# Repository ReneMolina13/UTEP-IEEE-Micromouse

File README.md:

<div id="top"></div>

<!-- PROJECT LOGO -->
</br>
<div align="center">
  
  <h3 align="center">UTEP IEEE Micromouse</h3>
   <p align="center">
     UTEP IEEE Micromouse project repository
     </br>
     <a href="workshops/Intro to micromouse presentation.pdf"><strong>See intro presentation</strong></a>
     </br>
  </p>
</div>

<!-- TABLE OF CONTENTS -->
<details>
  <summary>Table of Contents</summary>
  <ol>
    <li><a href="#about-the-project">About The Project</a></li>
    <li><a href="#contributing">Contributing</a></li>
    <li><a href="#license">License</a></li>
    <li><a href="#contact">Contact</a></li>
    <li><a href="#acknowledgments">Acknowledgments</a></li>
  </ol>
</details>

<!-- ABOUT THE PROJECT -->
## About The Project
</br>
<div align="left">
  IEEE UTEP Micromouse repository where you can find template code, schematics and workshops
  to build and get your mouse working. This repository was designed to be used with the micromouse
  kit shown in the schematics folder. The workshops will guide you through the necessary code to 
  have your mouse solving a micromouse maze.
  
  Take a look at:
  
  - [Schematics](micromouse_arduino_nano_kit/Micromouse_Arduino_Nano.pdf)
  - [Workshops](workshops/)
  - [Code](code_template/)
</div>

<p align="right">(<a href="#top">back to top</a>)</p>

<!-- CONTRIBUTING -->
## Contributing

To contribute, please fork the project and send a pull request or talk to any of the UTEP IEEE officers. For any other questions please use the contact info at the bottom to contact the owner of this repository.
<p align="right">(<a href="#top">back to top</a>)</p>

<!-- LICENSE -->
## License

Distributed under the MIT License. See `LICENSE.txt` for more information.

<p align="right">(<a href="#top">back to top</a>)</p>

<!-- CONTACT -->
## Contact

Alejandro Martinez Acosta - amartinezacosta@miners.utep.edu

Project Link: [https://github.com/amartinezacosta/UTEP-IEEE-Micromouse](https://github.com/amartinezacosta/UTEP-IEEE-Micromouse)

<p align="right">(<a href="#top">back to top</a>)</p>

<!-- ACKNOWLEDGMENTS -->
## Acknowledgments
[University of Texas at El Paso](https://www.utep.edu/)

[IEEE University of Texas at El Paso branch](https://edu.ieee.org/us-utep/)

<p align="right">(<a href="#top">back to top</a>)</p>

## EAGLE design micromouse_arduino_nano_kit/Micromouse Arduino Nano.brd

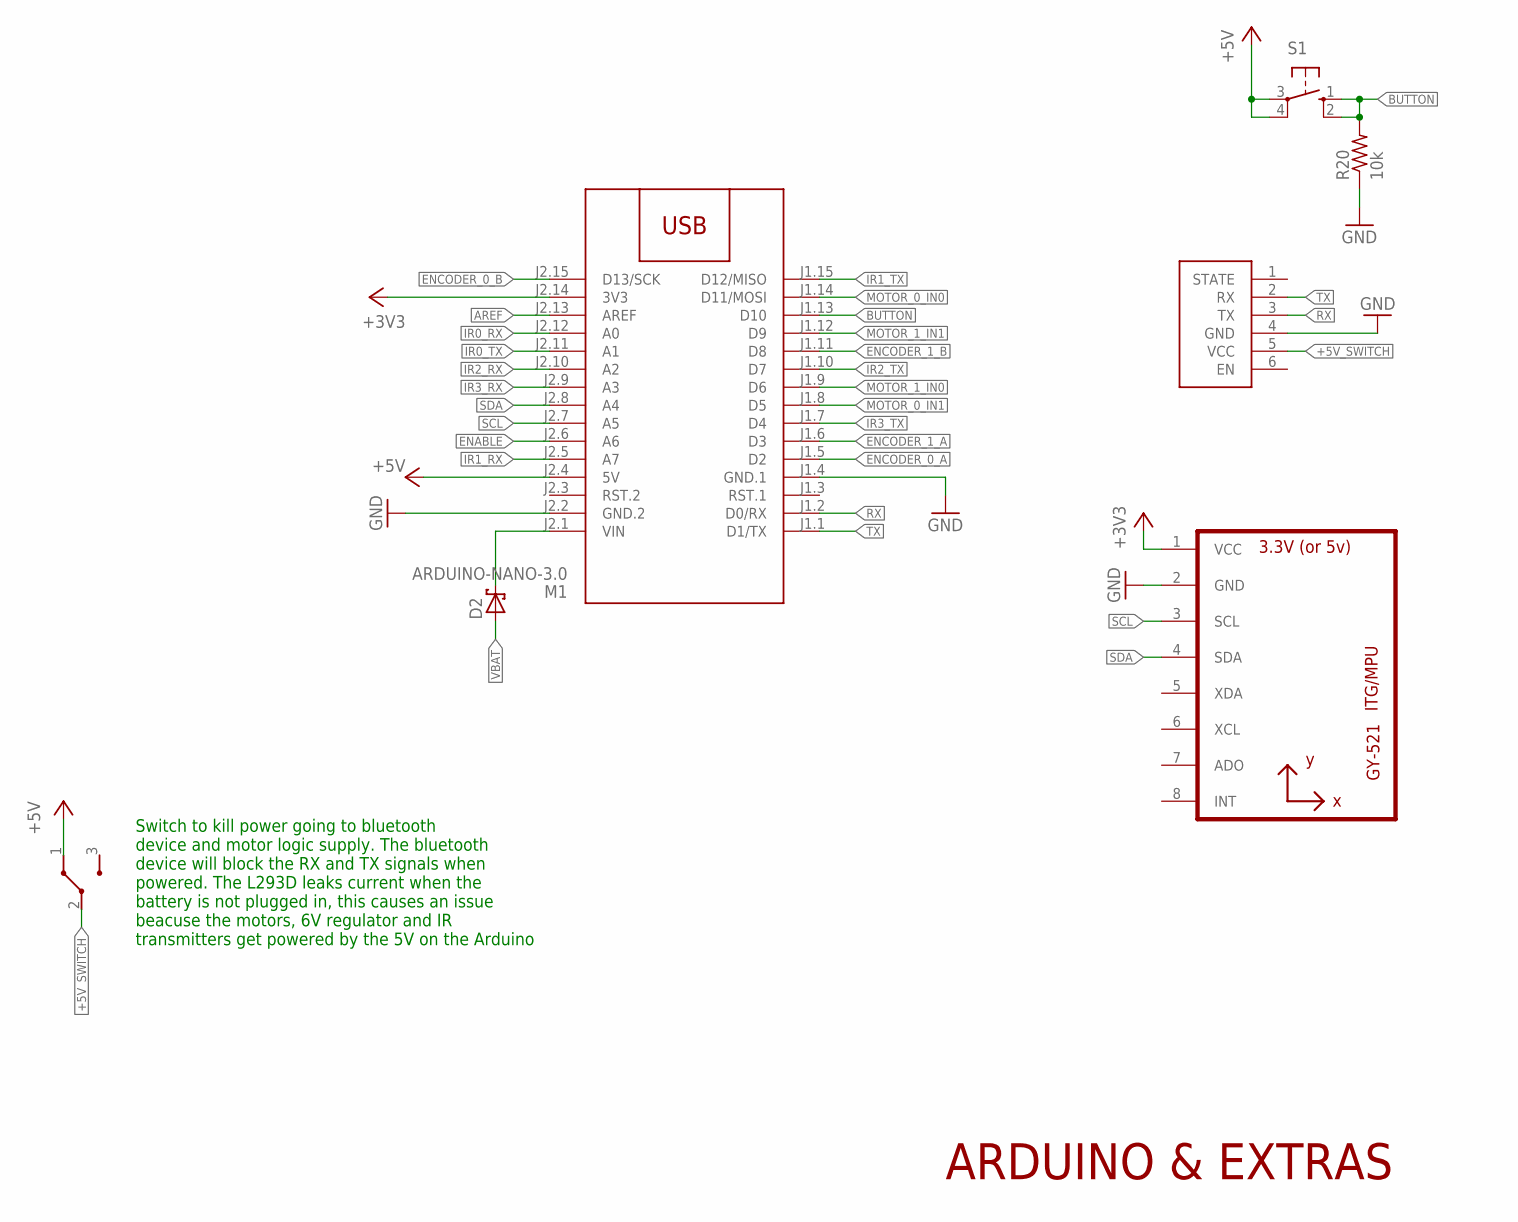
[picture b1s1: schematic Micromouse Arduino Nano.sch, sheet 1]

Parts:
D2: SCHOTTKY-DIODEDO41-7; DO41-7
M1: ARDUINO-NANO-3.0
R20: 10k; 0207/2V
S1: 10-XX; B3F-10XX
U1: GY-521MPU6050; GY-521
U$9: HC-05
U$10: K3-1260D

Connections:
+3V3: M1.J2.14 (3V3), U1.1 (VCC)
+5V: M1.J2.4 (5V), S1.3, S1.4 (P1), U$10.1; also elsewhere on the board
+5V_SWITCH: U$9.5 (VCC), U$10.2; also elsewhere on the board
AREF: M1.J2.13 (AREF)
BUTTON: M1.J1.13 (D10), R20.2, S1.1 (S), S1.2 (S1)
ENABLE: M1.J2.6 (A6); also elsewhere on the board
ENCODER_0_A: M1.J1.5 (D2); also elsewhere on the board
ENCODER_0_B: M1.J2.15 (D13/SCK); also elsewhere on the board
ENCODER_1_A: M1.J1.6 (D3); also elsewhere on the board
ENCODER_1_B: M1.J1.11 (D8); also elsewhere on the board
GND: M1.J1.4 (GND.1), M1.J2.2 (GND.2), R20.1, U1.2 (GND), U$9.4 (GND); also elsewhere on the board
IR0_RX: M1.J2.12 (A0); also elsewhere on the board
IR0_TX: M1.J2.11 (A1); also elsewhere on the board
IR1_RX: M1.J2.5 (A7); also elsewhere on the board
IR1_TX: M1.J1.15 (D12/MISO); also elsewhere on the board
IR2_RX: M1.J2.10 (A2); also elsewhere on the board
IR2_TX: M1.J1.10 (D7); also elsewhere on the board
IR3_RX: M1.J2.9 (A3); also elsewhere on the board
IR3_TX: M1.J1.7 (D4); also elsewhere on the board
MOTOR_0_IN0: M1.J1.14 (D11/MOSI); also elsewhere on the board
MOTOR_0_IN1: M1.J1.8 (D5); also elsewhere on the board
MOTOR_1_IN0: M1.J1.9 (D6); also elsewhere on the board
MOTOR_1_IN1: M1.J1.12 (D9); also elsewhere on the board
unnamed: D2.C, M1.J2.1 (VIN)
RX: M1.J1.2 (D0/RX), U$9.3 (TX)
SCL: M1.J2.7 (A5), U1.3 (SCL)
SDA: M1.J2.8 (A4), U1.4 (SDA)
TX: M1.J1.1 (D1/TX), U$9.2 (RX)
VBAT: D2.A; also elsewhere on the board

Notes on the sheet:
Switch to kill power going to bluetooth device and motor logic supply. The bluetooth device will block the RX and TX signals when powered. The L293D leaks current when the battery is not plugged in, this causes an issue beacuse the motors, 6V regulator and IR transmitters get powered by the 5V on t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
ARDUINO & EXTRAS

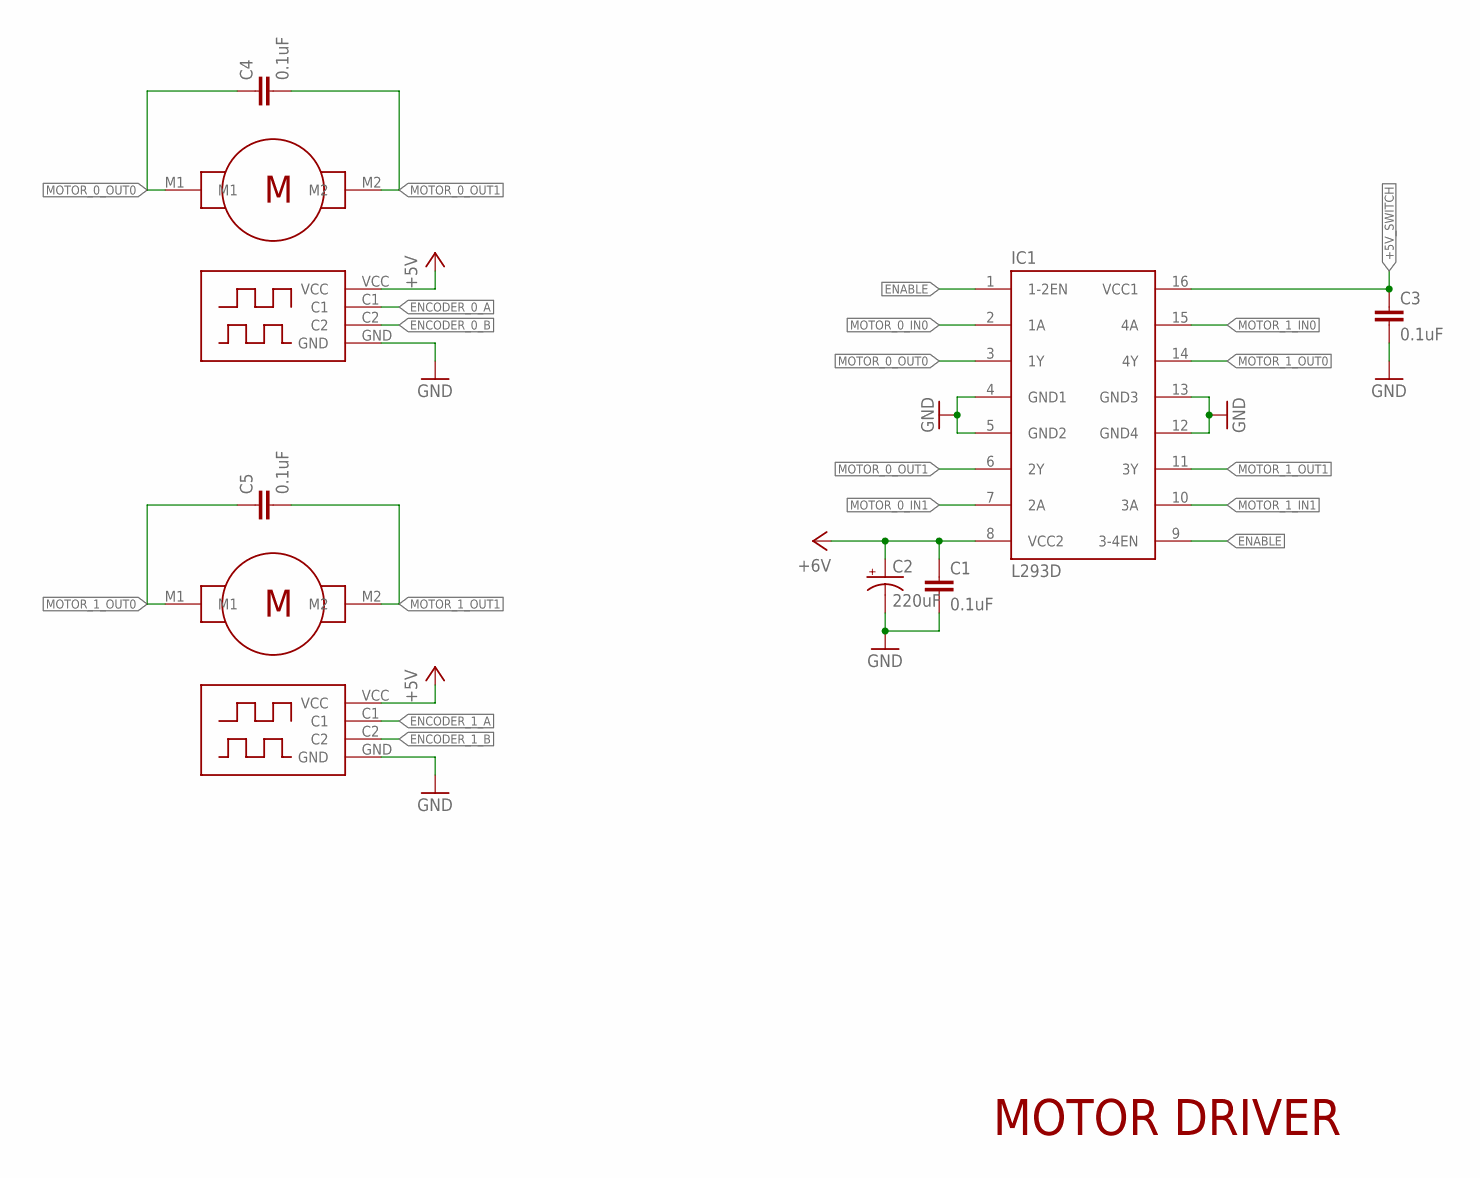
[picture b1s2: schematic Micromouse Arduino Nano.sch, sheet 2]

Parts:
C1, C3, C4, C5: 0.1uF; C050-025X075
C2: 220uF; E2,5-6
IC1: L293D; DIL16
U$1, U$2: DC_MOTOR

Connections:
+5V: U$1.VCC, U$2.VCC; also elsewhere on the board
+5V_SWITCH: C3.1, IC1.16 (VCC1); also elsewhere on the board
ENABLE: IC1.1 (1-2EN), IC1.9 (3-4EN); also elsewhere on the board
ENCODER_0_A: U$1.C1; also elsewhere on the board
ENCODER_0_B: U$1.C2; also elsewhere on the board
ENCODER_1_A: U$2.C1; also elsewhere on the board
ENCODER_1_B: U$2.C2; also elsewhere on the board
GND: C1.2, C2.-, C3.2, IC1.4 (GND1), IC1.5 (GND2), IC1.12 (GND4), IC1.13 (GND3), U$1.GND, U$2.GND; also elsewhere on the board
MOTOR_0_IN0: IC1.2 (1A); also elsewhere on the board
MOTOR_0_IN1: IC1.7 (2A); also elsewhere on the board
MOTOR_0_OUT0: C4.1, IC1.3 (1Y), U$1.M1
MOTOR_0_OUT1: C4.2, IC1.6 (2Y), U$1.M2
MOTOR_1_IN0: IC1.15 (4A); also elsewhere on the board
MOTOR_1_IN1: IC1.10 (3A); also elsewhere on the board
MOTOR_1_OUT0: C5.1, IC1.14 (4Y), U$2.M1
MOTOR_1_OUT1: C5.2, IC1.11 (3Y), U$2.M2
VCC: C1.1, C2.+, IC1.8 (VCC2); also elsewhere on the board

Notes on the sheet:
MOTOR DRIVER

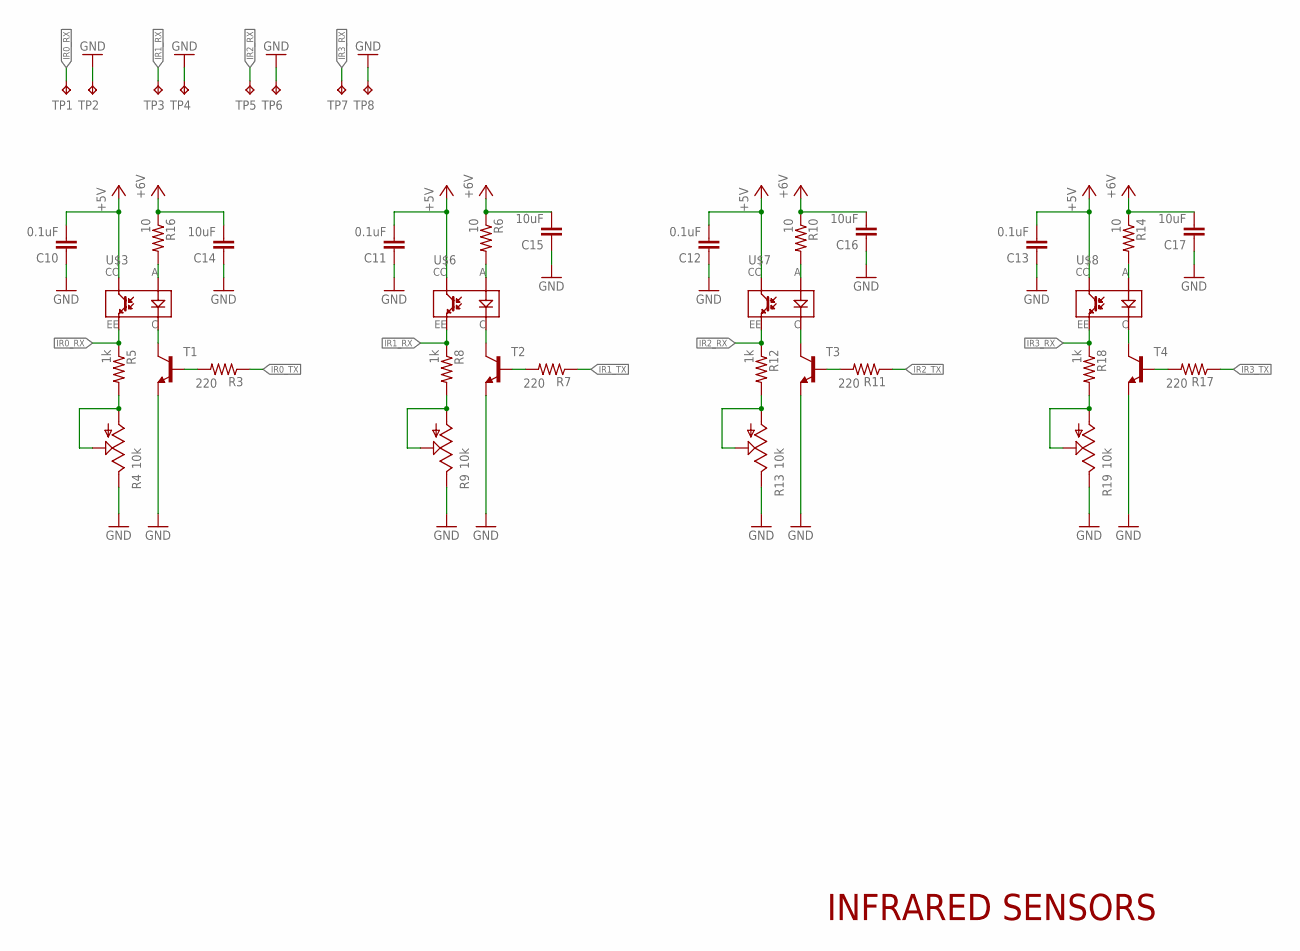
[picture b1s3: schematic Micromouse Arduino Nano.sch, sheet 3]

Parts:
C10, C11, C12, C13: 0.1uF; C050-025X075
C14, C15, C16, C17: 10uF; C050-025X075
R3, R7, R11, R17: 220; 0207/2V
R4, R9, R13, R19: 10k; CT6
R5, R8, R12, R18: 1k; 0207/2V
R6, R10, R14, R16: 10; 0207/2V
T1, T2, T3, T4: 2N4124-NPN-TO92-CBE; TO92-CBE
TP1, TP2, TP3, TP4, TP5, TP6, TP7, TP8: TPPAD1-13; P1-13
U$3, U$6, U$7, U$8: IR_DISTANCE_1X2

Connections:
+5V: C10.2, C11.2, C12.2, C13.2, U$3.CC, U$6.CC, U$7.CC, U$8.CC; also elsewhere on the board
GND: C10.1, C11.1, C12.1, C13.1, C14.1, C15.1, C16.1, C17.1, R4.E, R9.E, R13.E, R19.E, T1.E, T2.E, T3.E, T4.E, TP2.TP, TP4.TP, TP6.TP, TP8.TP; also elsewhere on the board
IR0_RX: R5.1, TP1.TP, U$3.EE; also elsewhere on the board
IR0_TX: R3.1; also elsewhere on the board
IR1_RX: R8.1, TP3.TP, U$6.EE; also elsewhere on the board
IR1_TX: R7.1; also elsewhere on the board
IR2_RX: R12.1, TP5.TP, U$7.EE; also elsewhere on the board
IR2_TX: R11.1; also elsewhere on the board
IR3_RX: R18.1, TP7.TP, U$8.EE; also elsewhere on the board
IR3_TX: R17.1; also elsewhere on the board
unnamed: T1.C, U$3.C
unnamed: R3.2, T1.B
unnamed: R16.2, U$3.A
unnamed: R6.2, U$6.A
unnamed: R4.A, R4.S, R5.2
unnamed: T2.C, U$6.C
unnamed: R7.2, T2.B
unnamed: R8.2, R9.A, R9.S
unnamed: R10.2, U$7.A
unnamed: T3.C, U$7.C
unnamed: R11.2, T3.B
unnamed: R12.2, R13.A, R13.S
unnamed: R14.2, U$8.A
unnamed: T4.C, U$8.C
unnamed: R17.2, T4.B
unnamed: R18.2, R19.A, R19.S
VCC: C14.2, C15.2, C16.2, C17.2, R6.1, R10.1, R14.1, R16.1; also elsewhere on the board

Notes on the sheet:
INFRARED SENSORS

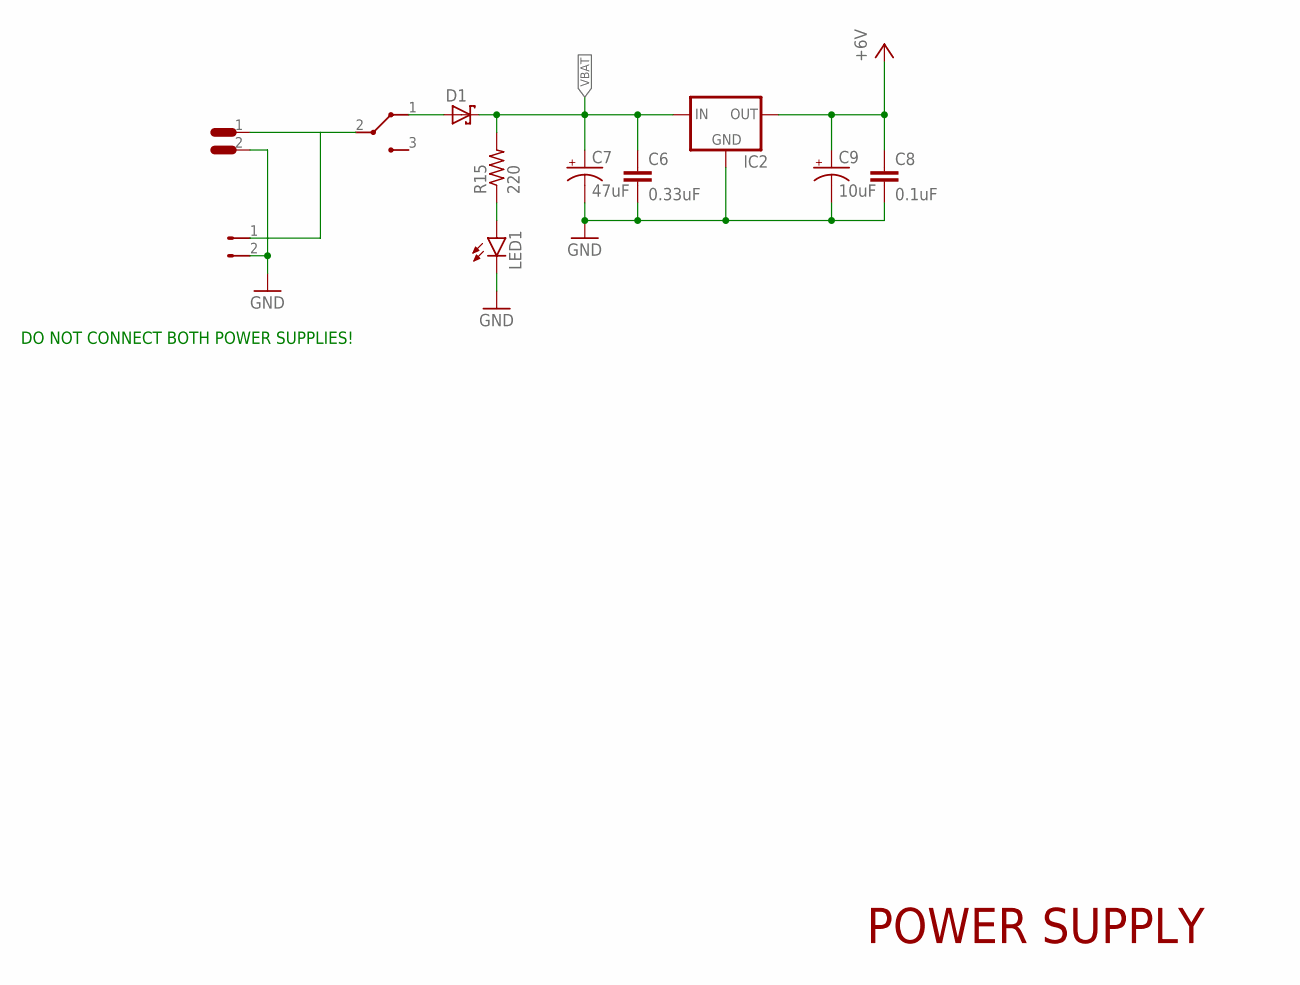
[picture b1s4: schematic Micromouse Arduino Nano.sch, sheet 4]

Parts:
C6: 0.33uF; C050-025X075
C7: 47uF; E2-4
C8: 0.1uF; C050-025X075
C9: 10uF; E2,5-5
D1: SCHOTTKY-DIODEDO41-7; DO41-7
IC2: 78XXS
LED1: LED5MM
R15: 220; 0207/2V
U$4: K3-1260D
U$5: XT30-M
U$12: JST_POWER

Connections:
GND: C6.2, C7.-, C8.2, C9.-, IC2.GND, LED1.K (C), U$5.2, U$12.2; also elsewhere on the board
unnamed: D1.A, U$4.1
unnamed: U$4.2, U$5.1, U$12.1
unnamed: LED1.A, R15.1
VBAT: C6.1, C7.+, D1.C, IC2.IN, R15.2; also elsewhere on the board
VCC: C8.1, C9.+, IC2.OUT; also elsewhere on the board

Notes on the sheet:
DO NOT CONNECT BOTH POWER SUPPLIES!
POWER SUPPLY

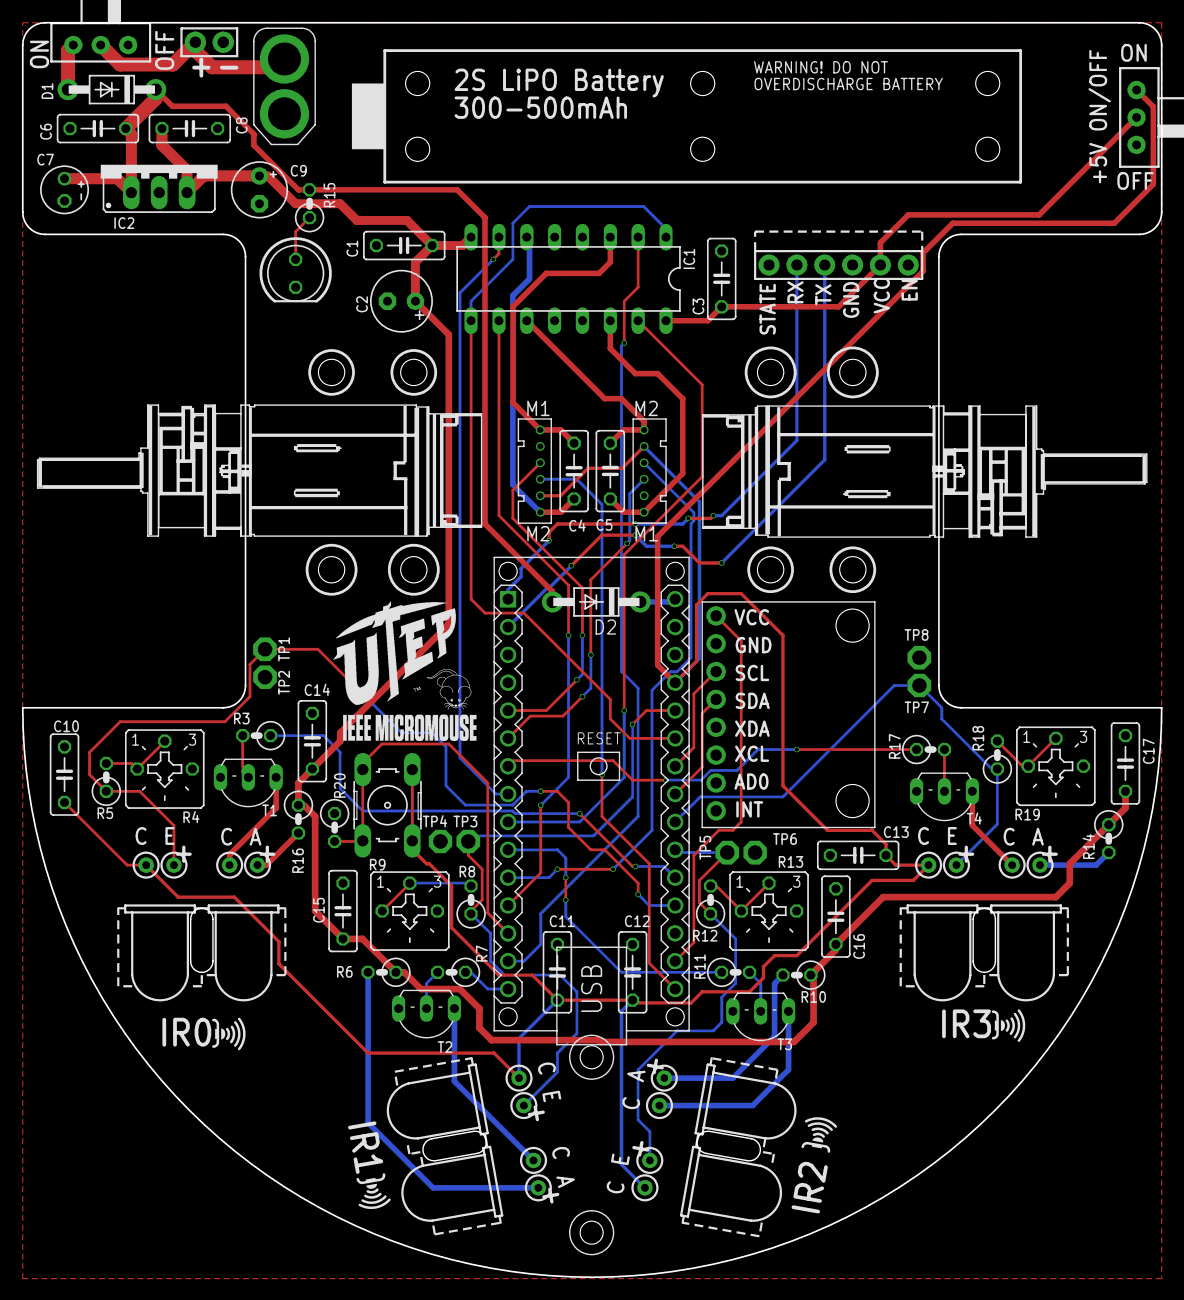
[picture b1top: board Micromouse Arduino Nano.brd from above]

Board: 2 copper layers, 103.9 x 114.4 mm, 76 parts (0 on the bottom side), 52 nets.

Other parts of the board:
U$11: CASTER_WHEEL
U$13: MICROMOUSE
U$14, U$15, U$16, U$17: IR_SENSOR
U$18: MICROMOUSE_TEXT
U$19: MINER_LOGO
U$20: MICROMOUSE_TEXT_1
U$21: LIPO

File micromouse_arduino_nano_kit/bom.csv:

Qty,Value,Device,Package,Parts,Description
1,,10-XX,B3F-10XX,S1,OMRON SWITCH
4,,2N4124-NPN-TO92-CBE,TO92-CBE,"T1, T2, T3, T4",NPN Transistror
1,,78XXS,78XXS,IC2,VOLTAGE REGULATOR
1,,LED5MM,LED5MM,LED1,LED
2,,SCHOTTKY-DIODEDO41-7,DO41-7,"D1, D2",Schottky Diode
9,0.1uF,C-EU050-025X075,C050-025X075,"C1, C3, C4, C5, C8, C10, C11, C12, C13","CAPACITOR, European symbol"
1,0.33uF,C-EU050-025X075,C050-025X075,C6,"CAPACITOR, European symbol"
4,10,R-US_0207/2V,0207/2V,"R6, R10, R14, R16","RESISTOR, American symbol"
1,10k,R-US_0207/2V,0207/2V,R20,"RESISTOR, American symbol"
4,10k,TRIM_US-CT6,CT6,"R4, R9, R13, R19",POTENTIOMETER
4,10uF,C-EU050-025X075,C050-025X075,"C14, C15, C16, C17","CAPACITOR, European symbol"
1,10uF,CPOL-USE2.5-5,"E2,5-5",C9,"POLARIZED CAPACITOR, American symbol"
4,1k,R-US_0207/2V,0207/2V,"R5, R8, R12, R18","RESISTOR, American symbol"
5,220,R-US_0207/2V,0207/2V,"R3, R7, R11, R15, R17","RESISTOR, American symbol"
1,220uF,CPOL-USE2.5-6,"E2,5-6",C2,"POLARIZED CAPACITOR, American symbol"
1,47uF,CPOL-USE2-4,E2-4,C7,"POLARIZED CAPACITOR, American symbol"
1,ARDUINO-NANO-3.0,ARDUINO-NANO-3.0,ARDUINO-NANO-3.0,M1,Arduino Nano 3.0 and compatible devices
2,DC_MOTOR,DC_MOTOR,DC_MOTOR,"U$1, U$2",
1,GY-521MPU6050,GY-521MPU6050,GY-521,U1,
1,HC-05,HC-05,HC-05,U$9,
4,IR_DISTANCE_1X2,IR_DISTANCE_1X2,IR_DISTANCE_1X2,"U$3, U$6, U$7, U$8",
1,JST_POWER,JST_POWER,JST_POWER,U$12,
2,K3-1260D,K3-1260D,K3-1260D,"U$4, U$10",
1,L293D,L293D,DIL16,IC1,PUSH-PULL 4 CHANNEL DRIVER
8,TPPAD1-13,TPPAD1-13,P1-13,"TP1, TP2, TP3, TP4, TP5, TP6, TP7, TP8",Test pad
1,XT30-M,XT30-M,XT30-M,U$5,

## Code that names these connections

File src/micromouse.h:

#ifndef MICROMOUSE_H_
#define MICROMOUSE_H_

#include <Arduino.h>
#include <stdbool.h>

/*Motor definitions*/
#define ENABLE            A6
#define MOTOR_0_1A        11
#define MOTOR_0_2A        5
#define MOTOR_1_1A        6  
#define MOTOR_1_2A        9
#define ENCODER_0_CHA     2
#define ENCODER_0_CHB     13
#define ENCODER_1_CHA     3
#define ENCODER_1_CHB     8

/*Infrared sensors definitions*/
#define IR0_TX       A1
#define IR1_TX       12
#define IR2_TX       7
#define IR3_TX       4
#define IR0_RX       A0
#define IR1_RX       A7
#define IR2_RX       A2
#define IR3_RX       A3

/*Extras*/
#define BUTTON      10

void motors_init(void);
void motor_0_speed(int speed, bool direction);
void motor_1_speed(int speed, bool direction);

void ir_init(void);
int ir_0_read(int delay);
int ir_1_read(int delay);
int ir_2_read(int delay);
int ir_3_read(int delay);

void gyro_init(void);

void control_forward(void);
void control_turn(float target_angle);

#endif

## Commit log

2022-02-01 Modified readme
2022-02-04 Workshop 7 Distance Control added
2022-02-04 Added images and modified README
2022-02-04 Added license and modified readme
2022-02-18 Workshop 8 added
2022-02-25 modified readdme
2022-03-04 added workshop 9
2022-03-04 modfified readme
2022-03-04 modified template code
2022-03-11 added src folder with micromouse and maze code
2022-03-11 Added workshop 10 intro to maze
2022-03-11 Fixed maze code and added maze source files to sketch template
2022-04-08 added week 11 workshopd, floodfill
2022-04-15 added workshop 12
2022-04-15 Added maze_get_cell function

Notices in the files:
parts and their libraries:
diy-modules: Released under the Creative Commons Attribution 4.0 International License: http://creativecommons.org/licenses/by/4.0
